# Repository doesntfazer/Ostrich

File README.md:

# Ostrich

34 key keyboard based on RP2040 with canted MCU.

This keyboard was inspired by the Reviung34 keyboard.

You can find the qmk firmware [here](https://github.com/doesntfazer/Keyboard-Dweebs-Firmware-repository/tree/main/QMK/ostrich)

If you are interested in using VIAL instead, (This is a GUI for qmk). Then please go [here](https://github.com/doesntfazer/Keyboard-Dweebs-Firmware-repository/tree/main/VIAL-QMK/ostrich)

It is important to note, the 0.9 version of this keyboard keyboard is built with an mcp23017-e/so MCP chip instead of using diodes.  
This chip requires pull-up resistors. Since this was meant to use an OLED, it just borrows the one built into the SSD1306. If you decide you don't want an OLED, you will need to solder pull up resistors on GP0 and GP1. (4.7k have been sufficient in my testing)

If you are using the 1.0 or later versions of this keyboard, the keyboards will use diodes, and you won't have to worry about it.

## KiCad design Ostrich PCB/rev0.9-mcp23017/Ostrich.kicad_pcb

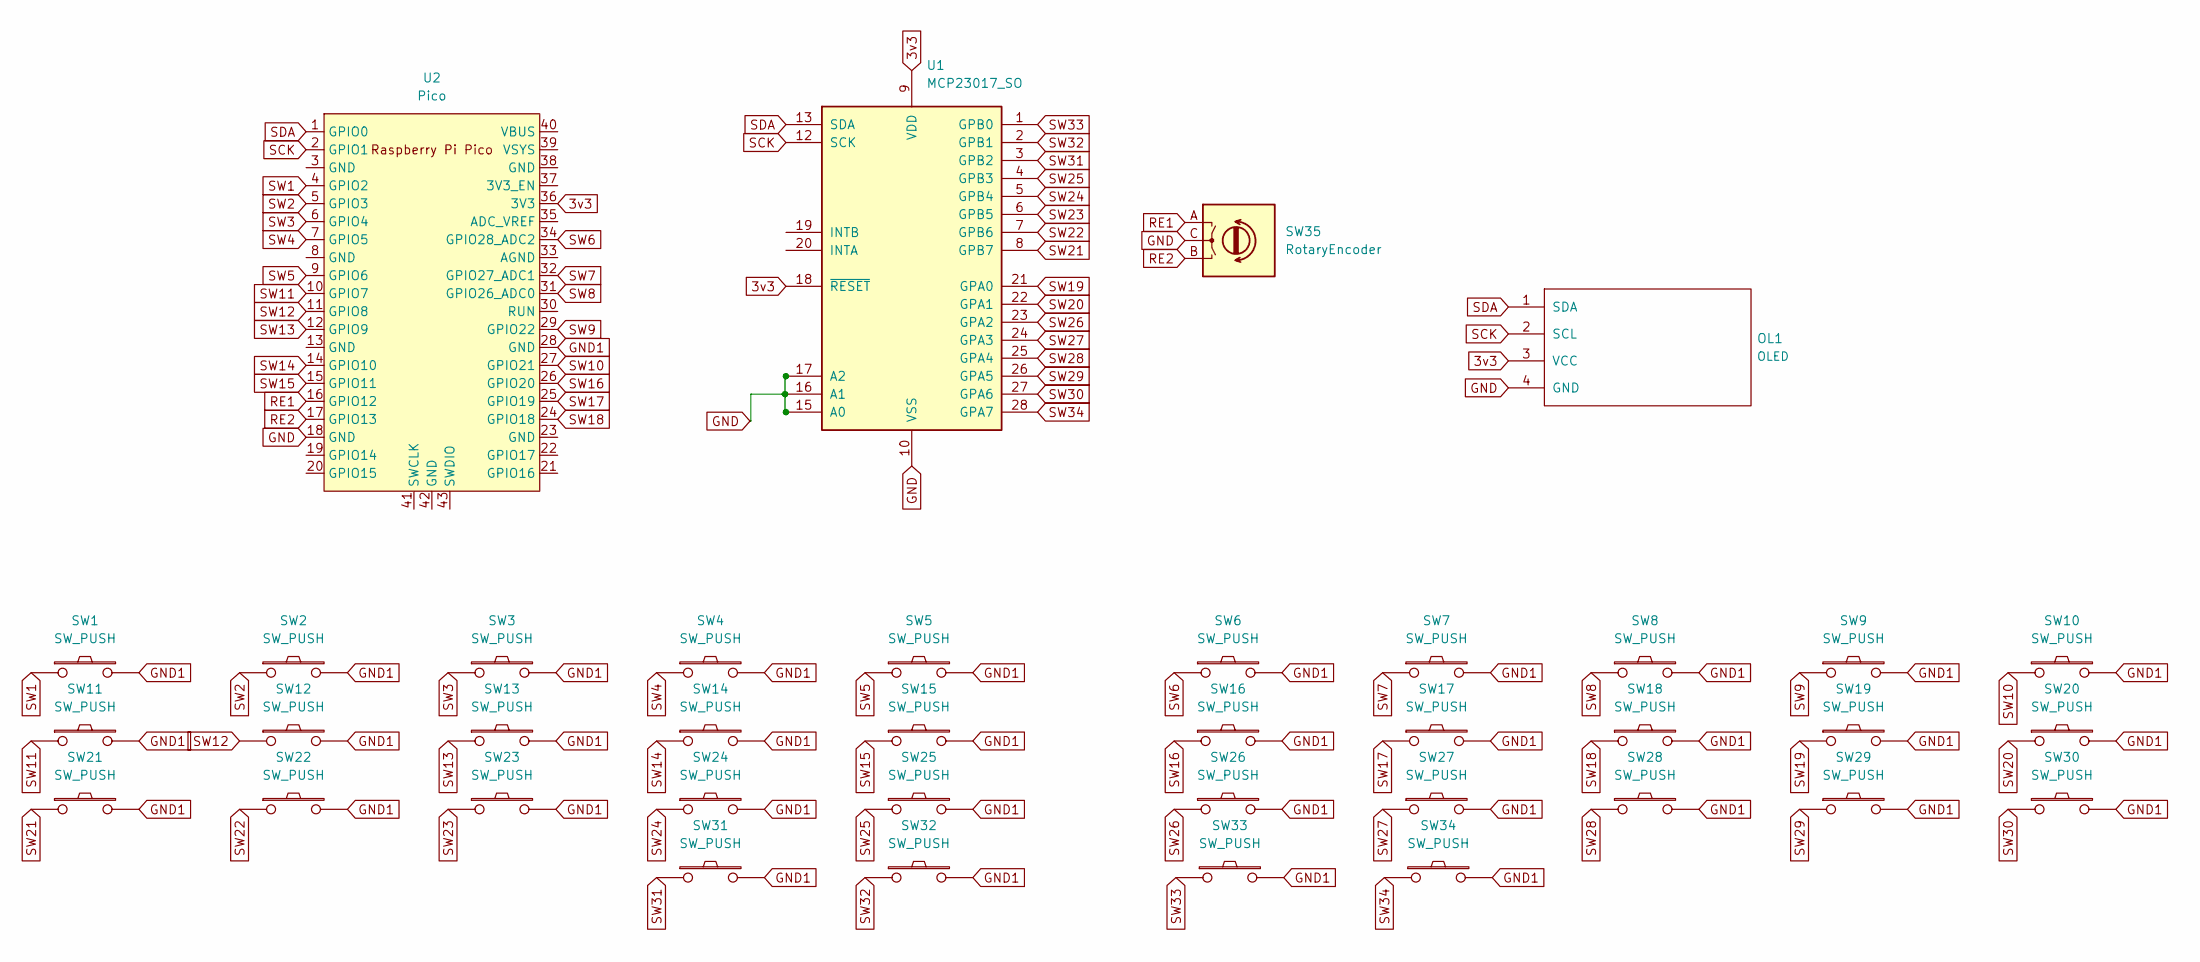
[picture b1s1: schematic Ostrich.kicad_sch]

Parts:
OL1: OLED; OLED_v2
SW1, SW2, SW3, SW4, SW5, SW6, SW7, SW8, SW9, SW10, SW11, SW12, SW13, SW14, SW15, SW16, SW17, SW18, SW19, SW20, SW21, SW22, SW23, SW24, SW25, SW26, SW27, SW28, SW29, SW30, SW31, SW32, SW33, SW34: SW_PUSH; CherryMX_Choc_1u-w3
SW35: RotaryEncoder; RotaryEncoder_Alps_EC12E_Vertical_H20mm
U1: MCP23017_SO; SOIC-28W_7.5x17.9mm_P1.27mm
U2: Pico; RPi_Pico_SMD_TH

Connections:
3v3: OL1.3 (VCC), U1.9 (VDD), U1.18 (~RESET), U2.36 (3V3)
GND: OL1.4 (GND), SW35.C, U1.10 (VSS), U1.15 (A0), U1.16 (A1), U1.17 (A2), U2.18 (GND)
GND1: SW1.2, SW2.2, SW3.2, SW4.2, SW5.2, SW6.2, SW7.2, SW8.2, SW9.2, SW10.2, SW11.2, SW12.2, SW13.2, SW14.2, SW15.2, SW16.2, SW17.2, SW18.2, SW19.2, SW20.2, SW21.2, SW22.2, SW23.2, SW24.2, SW25.2, SW26.2, SW27.2, SW28.2, SW29.2, SW30.2, SW31.2, SW32.2, SW33.2, SW34.2, U2.28 (GND)
RE1: SW35.A, U2.16 (GPIO12)
RE2: SW35.B, U2.17 (GPIO13)
SCK: OL1.2 (SCL), U1.12 (SCK), U2.2 (GPIO1)
SDA: OL1.1 (SDA), U1.13 (SDA), U2.1 (GPIO0)
SW1: SW1.1, U2.4 (GPIO2)
SW2: SW2.1, U2.5 (GPIO3)
SW3: SW3.1, U2.6 (GPIO4)
SW4: SW4.1, U2.7 (GPIO5)
SW5: SW5.1, U2.9 (GPIO6)
SW6: SW6.1, U2.34 (GPIO28_ADC2)
SW7: SW7.1, U2.32 (GPIO27_ADC1)
SW8: SW8.1, U2.31 (GPIO26_ADC0)
SW9: SW9.1, U2.29 (GPIO22)
SW10: SW10.1, U2.27 (GPIO21)
SW11: SW11.1, U2.10 (GPIO7)
SW12: SW12.1, U2.11 (GPIO8)
SW13: SW13.1, U2.12 (GPIO9)
SW14: SW14.1, U2.14 (GPIO10)
SW15: SW15.1, U2.15 (GPIO11)
SW16: SW16.1, U2.26 (GPIO20)
SW17: SW17.1, U2.25 (GPIO19)
SW18: SW18.1, U2.24 (GPIO18)
SW19: SW19.1, U1.21 (GPA0)
SW20: SW20.1, U1.22 (GPA1)
SW21: SW21.1, U1.8 (GPB7)
SW22: SW22.1, U1.7 (GPB6)
SW23: SW23.1, U1.6 (GPB5)
SW24: SW24.1, U1.5 (GPB4)
SW25: SW25.1, U1.4 (GPB3)
SW26: SW26.1, U1.23 (GPA2)
SW27: SW27.1, U1.24 (GPA3)
SW28: SW28.1, U1.25 (GPA4)
SW29: SW29.1, U1.26 (GPA5)
SW30: SW30.1, U1.27 (GPA6)
SW31: SW31.1, U1.3 (GPB2)
SW32: SW32.1, U1.2 (GPB1)
SW33: SW33.1, U1.1 (GPB0)
SW34: SW34.1, U1.28 (GPA7)

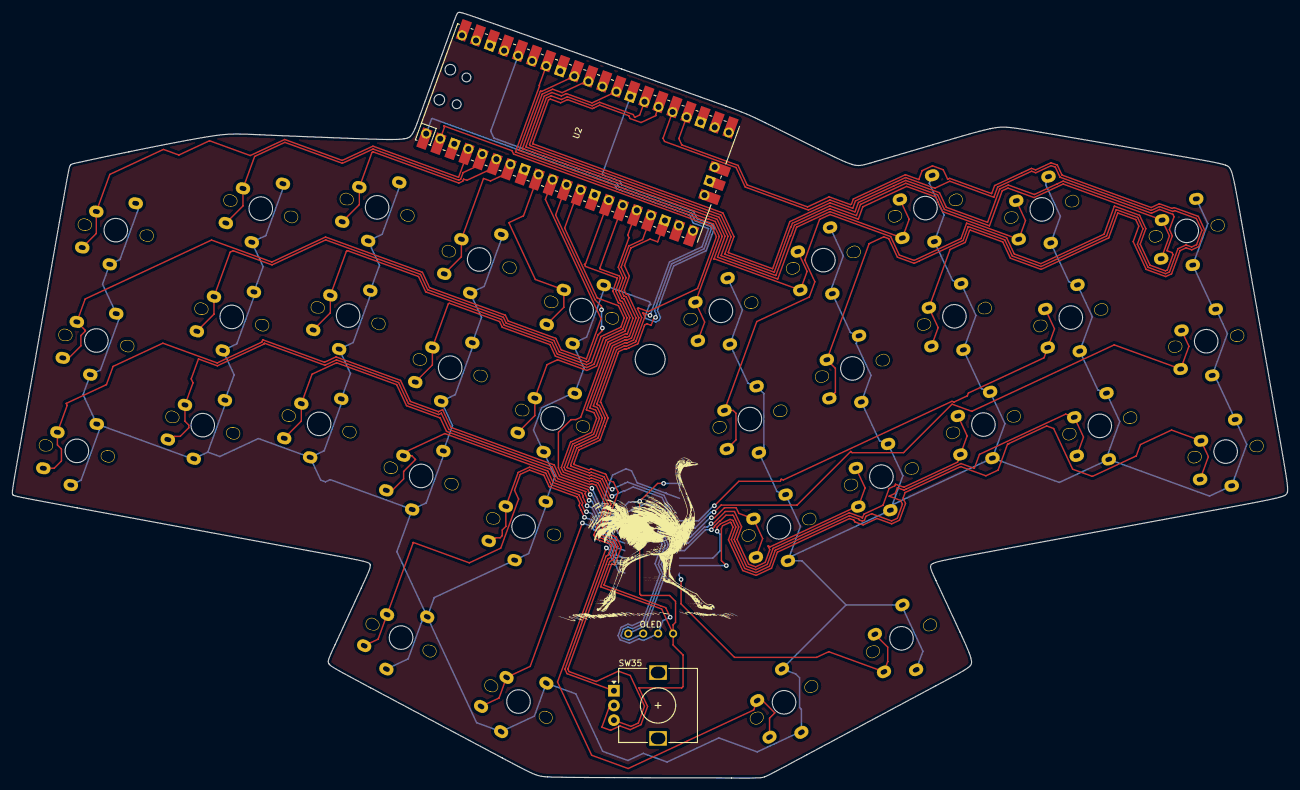
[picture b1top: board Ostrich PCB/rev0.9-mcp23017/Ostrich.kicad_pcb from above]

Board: 2 copper layers, 216.8 x 130.2 mm, 38 parts (1 on the bottom side), 41 nets.

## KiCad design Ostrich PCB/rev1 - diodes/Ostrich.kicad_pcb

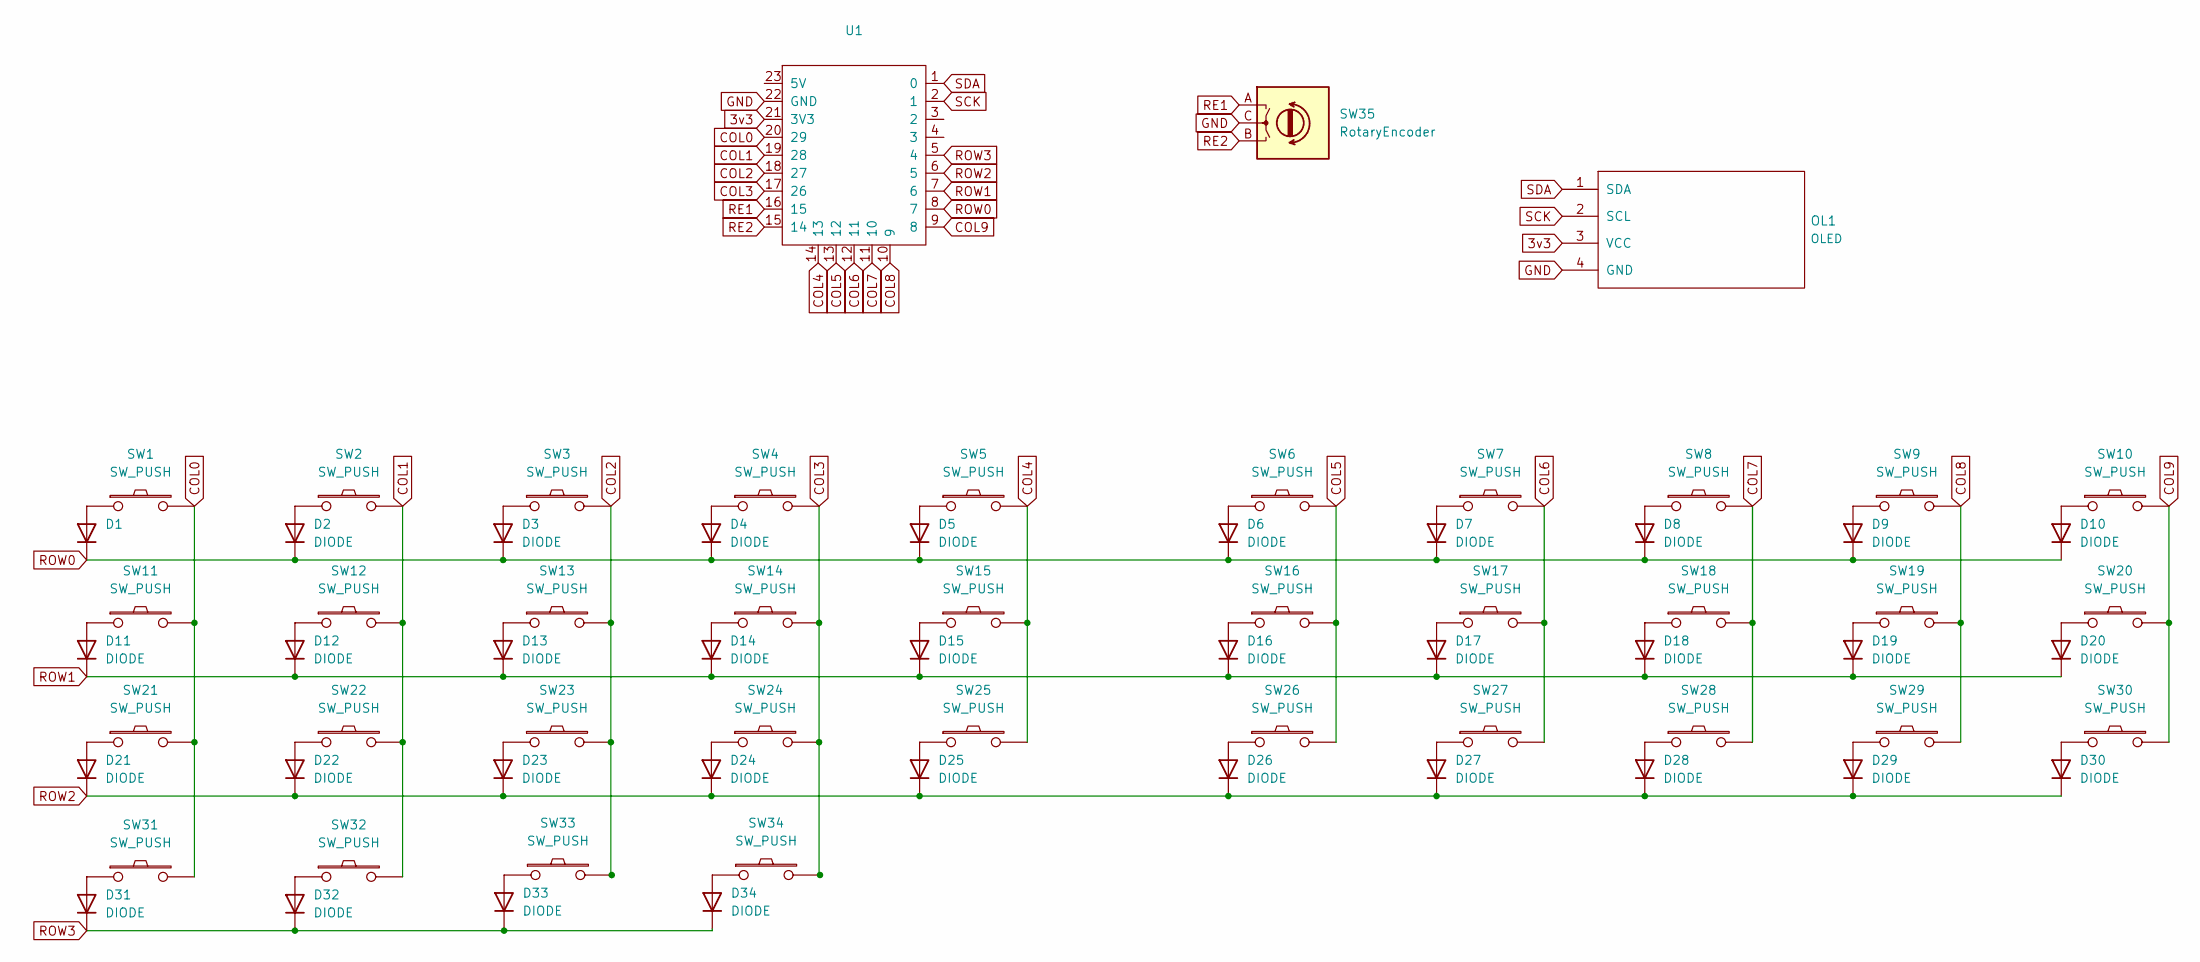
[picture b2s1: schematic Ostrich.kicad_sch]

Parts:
D1: (no value)
D2, D3, D4, D5, D6, D7, D8, D9, D10, D11, D12, D13, D14, D15, D16, D17, D18, D19, D20, D21, D22, D23, D24, D25, D26, D27, D28, D29, D30, D31, D32, D33, D34: DIODE
OL1: OLED; OLED_v2
SW1, SW2, SW3, SW4, SW5, SW6, SW7, SW8, SW9, SW10, SW11, SW12, SW13, SW14, SW15, SW16, SW17, SW18, SW19, SW20, SW21, SW22, SW23, SW24, SW25, SW26, SW27, SW28, SW29, SW30, SW31, SW32, SW33, SW34: SW_PUSH; CherryMX_Choc_1u-w3
SW35: RotaryEncoder; RotaryEncoder_Alps_EC12E_Vertical_H20mm
U1: (no value)

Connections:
3v3: OL1.3 (VCC), U1.21 (3V3)
COL0: SW1.2, SW11.2, SW21.2, SW31.2, U1.20 (29)
COL1: SW2.2, SW12.2, SW22.2, SW32.2, U1.19 (28)
COL2: SW3.2, SW13.2, SW23.2, SW33.2, U1.18 (27)
COL3: SW4.2, SW14.2, SW24.2, SW34.2, U1.17 (26)
COL4: SW5.2, SW15.2, SW25.2, U1.14 (13)
COL5: SW6.2, SW16.2, SW26.2, U1.13 (12)
COL6: SW7.2, SW17.2, SW27.2, U1.12 (11)
COL7: SW8.2, SW18.2, SW28.2, U1.11 (10)
COL8: SW9.2, SW19.2, SW29.2, U1.10 (9)
COL9: SW10.2, SW20.2, SW30.2, U1.9 (8)
GND: OL1.4 (GND), SW35.C, U1.22 (GND)
unnamed: D32.1 (A), SW32.1
unnamed: D1.1 (A), SW1.1
unnamed: D2.1 (A), SW2.1
unnamed: D3.1 (A), SW3.1
unnamed: D4.1 (A), SW4.1
unnamed: D5.1 (A), SW5.1
unnamed: D6.1 (A), SW6.1
unnamed: D7.1 (A), SW7.1
unnamed: D8.1 (A), SW8.1
unnamed: D9.1 (A), SW9.1
unnamed: D10.1 (A), SW10.1
unnamed: D11.1 (A), SW11.1
unnamed: D12.1 (A), SW12.1
unnamed: D13.1 (A), SW13.1
unnamed: D14.1 (A), SW14.1
unnamed: D15.1 (A), SW15.1
unnamed: D16.1 (A), SW16.1
unnamed: D17.1 (A), SW17.1
unnamed: D18.1 (A), SW18.1
unnamed: D19.1 (A), SW19.1
unnamed: D20.1 (A), SW20.1
unnamed: D21.1 (A), SW21.1
unnamed: D22.1 (A), SW22.1
unnamed: D23.1 (A), SW23.1
unnamed: D24.1 (A), SW24.1
unnamed: D25.1 (A), SW25.1
unnamed: D26.1 (A), SW26.1
unnamed: D27.1 (A), SW27.1
unnamed: D28.1 (A), SW28.1
unnamed: D29.1 (A), SW29.1
unnamed: D30.1 (A), SW30.1
unnamed: D31.1 (A), SW31.1
unnamed: D33.1 (A), SW33.1
unnamed: D34.1 (A), SW34.1
RE1: SW35.A, U1.16 (15)
RE2: SW35.B, U1.15 (14)
ROW0: D1.2 (K), D2.2 (K), D3.2 (K), D4.2 (K), D5.2 (K), D6.2 (K), D7.2 (K), D8.2 (K), D9.2 (K), D10.2 (K), U1.8 (7)
ROW1: D11.2 (K), D12.2 (K), D13.2 (K), D14.2 (K), D15.2 (K), D16.2 (K), D17.2 (K), D18.2 (K), D19.2 (K), D20.2 (K), U1.7 (6)
ROW2: D21.2 (K), D22.2 (K), D23.2 (K), D24.2 (K), D25.2 (K), D26.2 (K), D27.2 (K), D28.2 (K), D29.2 (K), D30.2 (K), U1.6 (5)
ROW3: D31.2 (K), D32.2 (K), D33.2 (K), D34.2 (K), U1.5 (4)
SCK: OL1.2 (SCL), U1.2 (1)
SDA: OL1.1 (SDA), U1.1 (0)

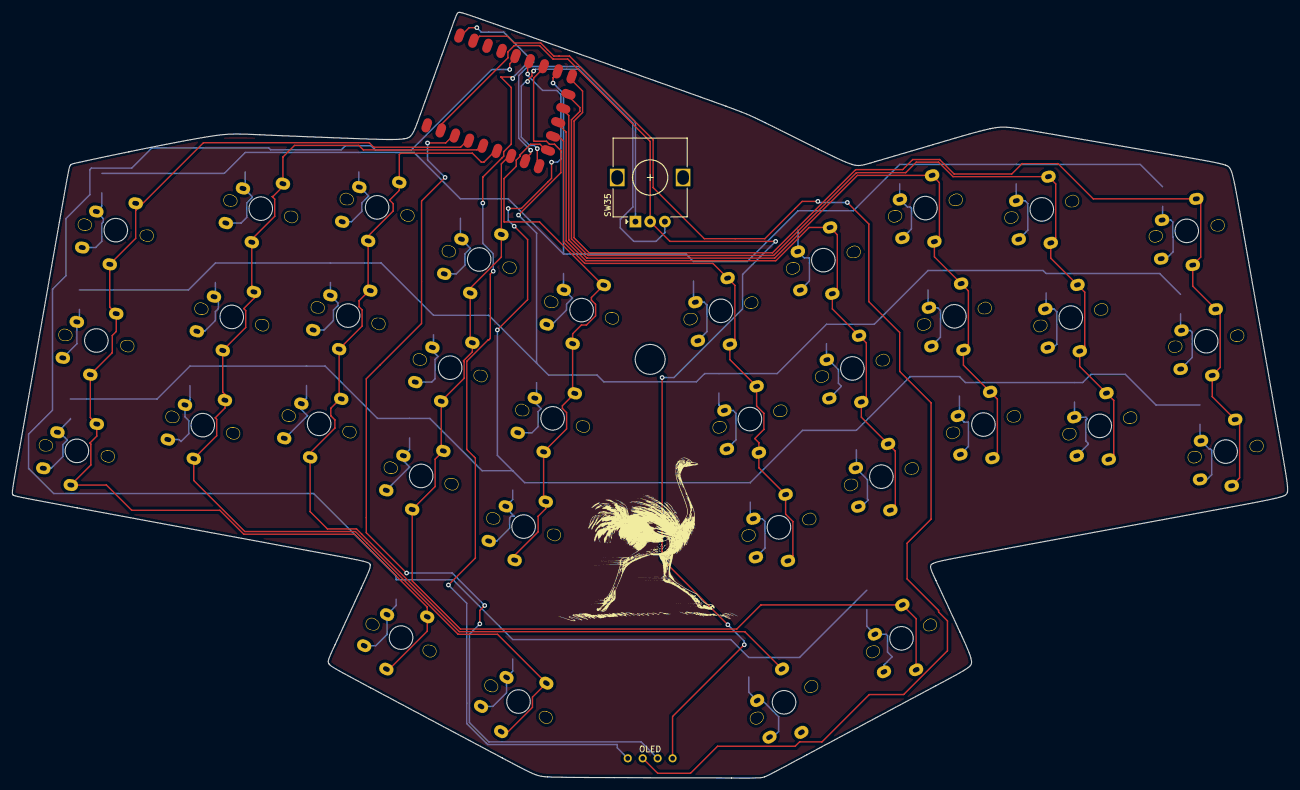
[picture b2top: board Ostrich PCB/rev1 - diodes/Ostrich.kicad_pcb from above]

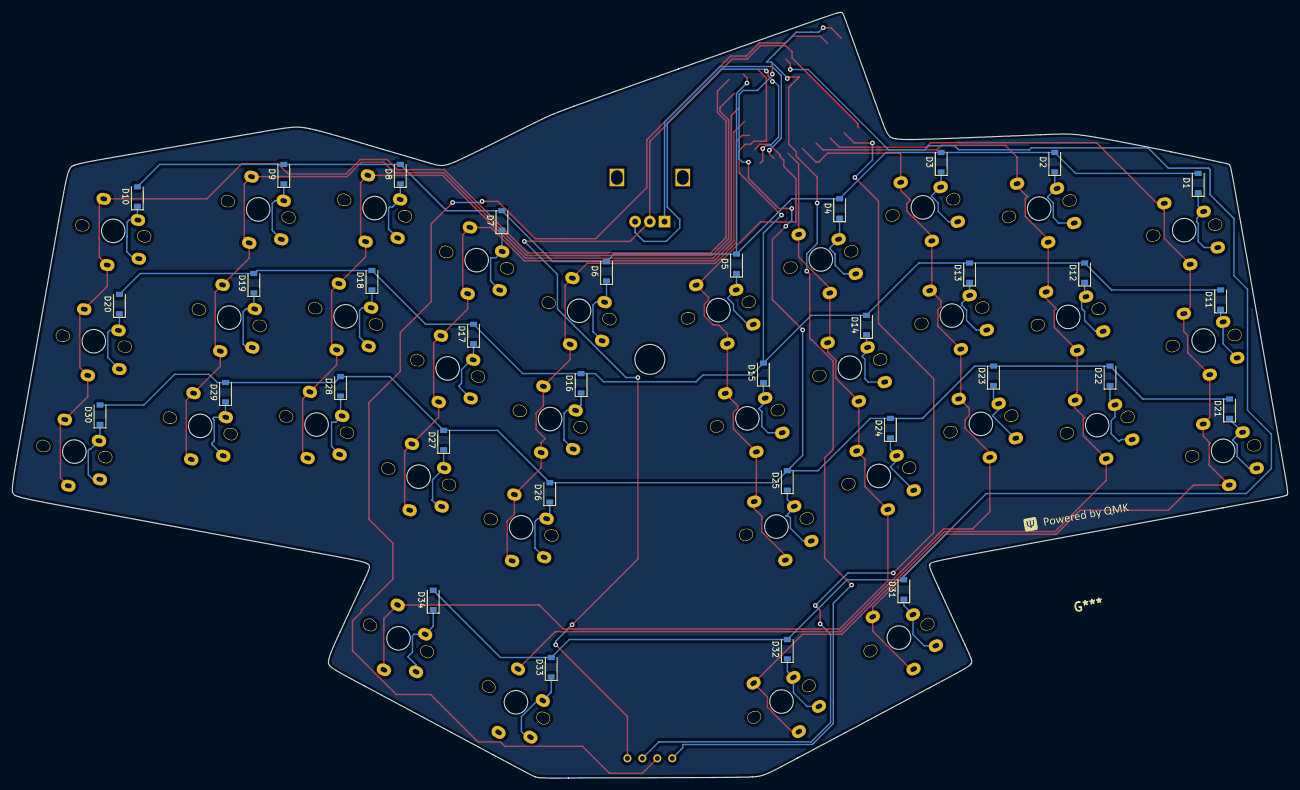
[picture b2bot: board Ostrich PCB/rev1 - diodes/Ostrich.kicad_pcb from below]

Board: 2 copper layers, 216.8 x 130.2 mm, 71 parts (34 on the bottom side), 54 nets.

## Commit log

2023-03-21 edit readme
